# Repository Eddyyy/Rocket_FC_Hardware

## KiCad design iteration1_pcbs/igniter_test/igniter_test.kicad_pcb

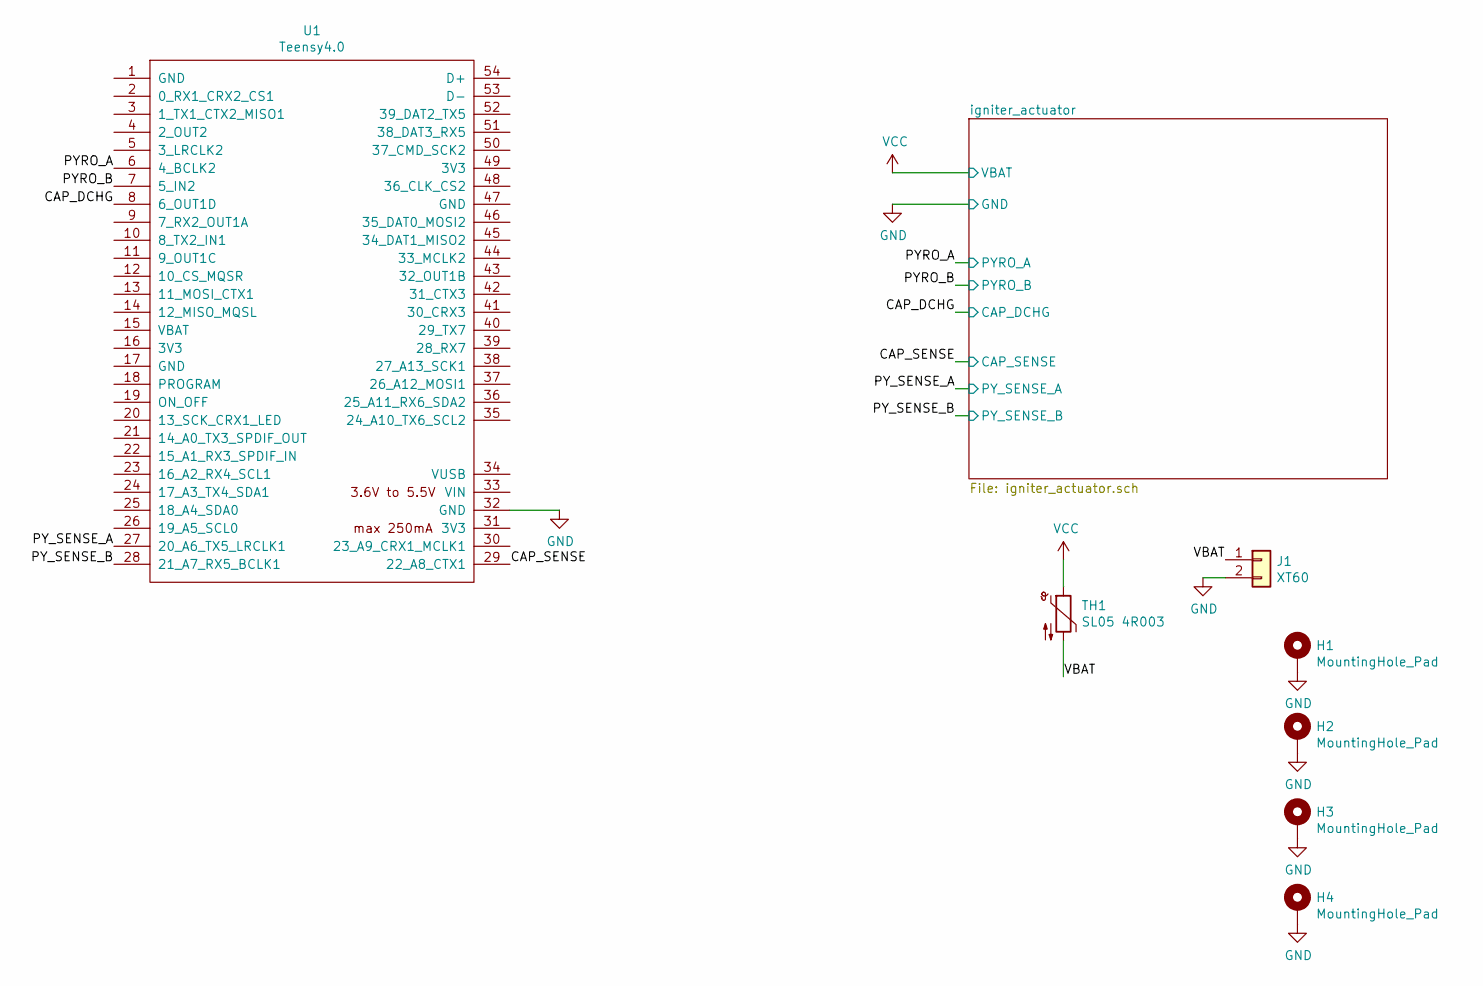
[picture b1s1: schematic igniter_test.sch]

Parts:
H1, H2, H3, H4: MountingHole_Pad; MountingHole_3.2mm_M3_Pad_Via
J1: XT60; AMASS_XT60-M_1x02_P7.20mm_Vertical
TH1: SL05 4R003; SL05_4R003
U1: Teensy4.0; Teensy40

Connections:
/CAP_DCHG: U1.8 (6_OUT1D); also elsewhere on the board
/CAP_SENSE: U1.29 (22_A8_CTX1); also elsewhere on the board
/PYRO_A: U1.6 (4_BCLK2); also elsewhere on the board
/PYRO_B: U1.7 (5_IN2); also elsewhere on the board
/PY_SENSE_A: U1.27 (20_A6_TX5_LRCLK1); also elsewhere on the board
/PY_SENSE_B: U1.28 (21_A7_RX5_BCLK1); also elsewhere on the board
/VBAT: J1.1, TH1.2
GND: H1.1, H2.1, H3.1, H4.1, J1.2, U1.32 (GND); also elsewhere on the board
VCC: TH1.1; also elsewhere on the board

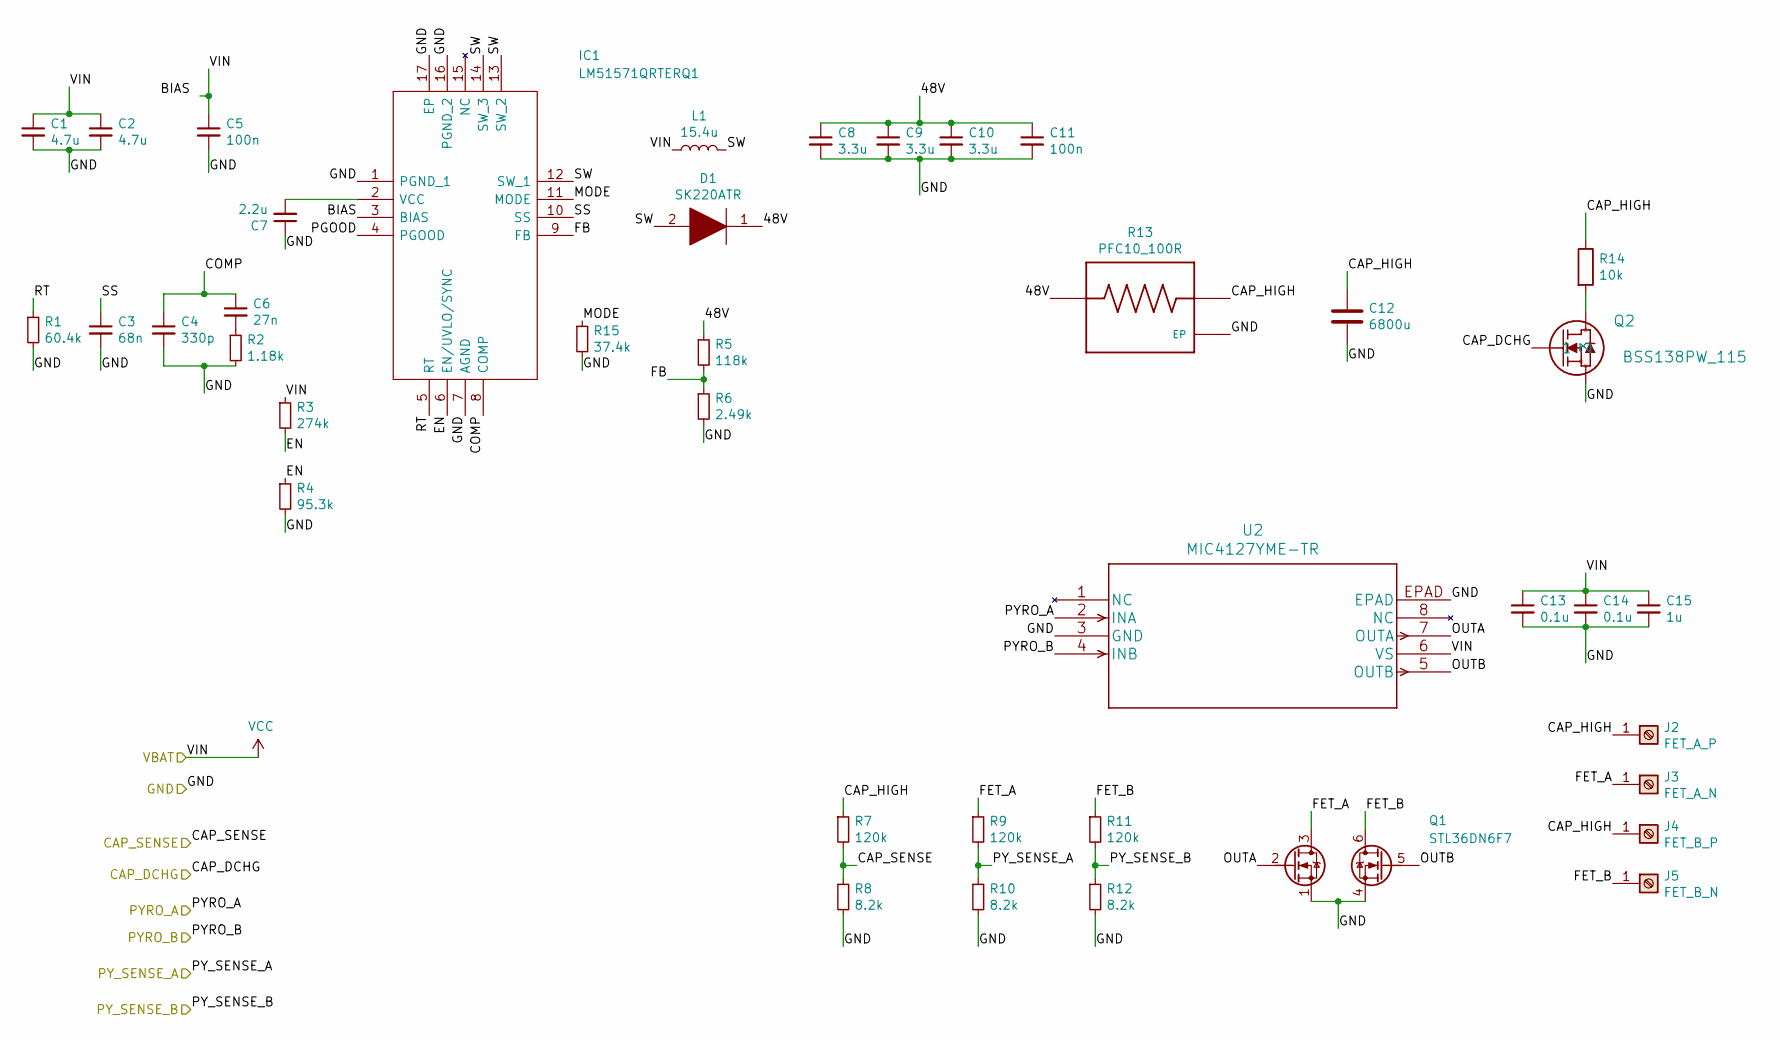
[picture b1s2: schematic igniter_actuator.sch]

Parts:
C1, C2: 4.7u; C_0805_2012Metric_Pad1.18x1.45mm_HandSolder
C3: 68n; C_0603_1608Metric_Pad1.08x0.95mm_HandSolder
C4: 330p; C_0603_1608Metric_Pad1.08x0.95mm_HandSolder
C5, C11: 100n; C_0805_2012Metric_Pad1.18x1.45mm_HandSolder
C6: 27n; C_0805_2012Metric_Pad1.18x1.45mm_HandSolder
C7: 2.2u; C_0805_2012Metric_Pad1.18x1.45mm_HandSolder
C8, C9, C10: 3.3u; C_1206_3216Metric_Pad1.33x1.80mm_HandSolder
C12: 6800u; UVR1H682MRD6
C13, C14: 0.1u; C_0603_1608Metric_Pad1.08x0.95mm_HandSolder
C15: 1u; C_0603_1608Metric_Pad1.08x0.95mm_HandSolder
D1: SK220ATR
IC1: LM51571QRTERQ1
J2: FET_A_P; SM99S01VBNN05G7
J3: FET_A_N; SM99S01VBNN05G7
J4: FET_B_P; SM99S01VBNN05G7
J5: FET_B_N; SM99S01VBNN05G7
L1: 15.4u; L_Wuerth_HCI-1365
Q1: STL36DN6F7; VDFN_5x6
Q2: BSS138PW_115
R1: 60.4k; R_0603_1608Metric_Pad0.98x0.95mm_HandSolder
R2: 1.18k; R_0603_1608Metric_Pad0.98x0.95mm_HandSolder
R3: 274k; R_0603_1608Metric_Pad0.98x0.95mm_HandSolder
R4: 95.3k; R_0603_1608Metric_Pad0.98x0.95mm_HandSolder
R5: 118k; R_0603_1608Metric_Pad0.98x0.95mm_HandSolder
R6: 2.49k; R_0603_1608Metric_Pad0.98x0.95mm_HandSolder
R7, R9, R11: 120k; R_0603_1608Metric_Pad0.98x0.95mm_HandSolder
R8, R10, R12: 8.2k; R_0603_1608Metric_Pad0.98x0.95mm_HandSolder
R13: PFC10_100R; RES_PFC10
R14: 10k; R_0805_2012Metric_Pad1.20x1.40mm_HandSolder
R15: 37.4k; R_0603_1608Metric_Pad0.98x0.95mm_HandSolder
U2: MIC4127YME-TR

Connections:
/CAP_DCHG: Q2.1; also elsewhere on the board
/CAP_SENSE: R7.2, R8.1; also elsewhere on the board
/PYRO_A: U2.2 (INA); also elsewhere on the board
/PYRO_B: U2.4 (INB); also elsewhere on the board
/PY_SENSE_A: R9.2, R10.1; also elsewhere on the board
/PY_SENSE_B: R11.2, R12.1; also elsewhere on the board
/igniter_actuator/48V: C8.1, C9.1, C10.1, C11.1, D1.1, R5.1, R13.1
/igniter_actuator/BIAS: IC1.3 (BIAS)
/igniter_actuator/CAP_HIGH: C12.1, J2.1, J4.1, R7.1, R13.2, R14.1
/igniter_actuator/COMP: C4.1, C6.1, IC1.8 (COMP)
/igniter_actuator/EN: IC1.6 (EN/UVLO/SYNC), R3.2, R4.1
/igniter_actuator/FB: IC1.9 (FB), R5.2, R6.1
/igniter_actuator/FET_A: J3.1, Q1.3 (D), R9.1
/igniter_actuator/FET_B: J5.1, Q1.6 (D), R11.1
/igniter_actuator/MODE: IC1.11 (MODE), R15.1
/igniter_actuator/OUTA: Q1.2 (G), U2.7 (OUTA)
/igniter_actuator/OUTB: Q1.5 (G), U2.5 (OUTB)
/igniter_actuator/PGOOD: IC1.4 (PGOOD)
/igniter_actuator/RT: IC1.5 (RT), R1.1
/igniter_actuator/SS: C3.1, IC1.10 (SS)
/igniter_actuator/SW: D1.2, IC1.12 (SW_1), IC1.13 (SW_2), IC1.14 (SW_3), L1.2
GND: C1.2, C2.2, C3.2, C4.2, C5.2, C7.1, C8.2, C9.2, C10.2, C11.2, C12.2, C13.2, C14.2, C15.2, IC1.1 (PGND_1), IC1.7 (AGND), IC1.16 (PGND_2), IC1.17 (EP), Q1.1 (S), Q1.4 (S), Q2.2, R1.2, R2.2, R4.2, R6.2, R8.2, R10.2, R12.2, R13.3 (EP), R15.2, U2.3 (GND), U2.EPAD; also elsewhere on the board
unnamed: C6.2, R2.1
unnamed: C7.2, IC1.2 (VCC)
unnamed: Q2.3, R14.2
VCC: C1.1, C2.1, C5.1, C13.1, C14.1, C15.1, L1.1, R3.1, U2.6 (VS); also elsewhere on the board

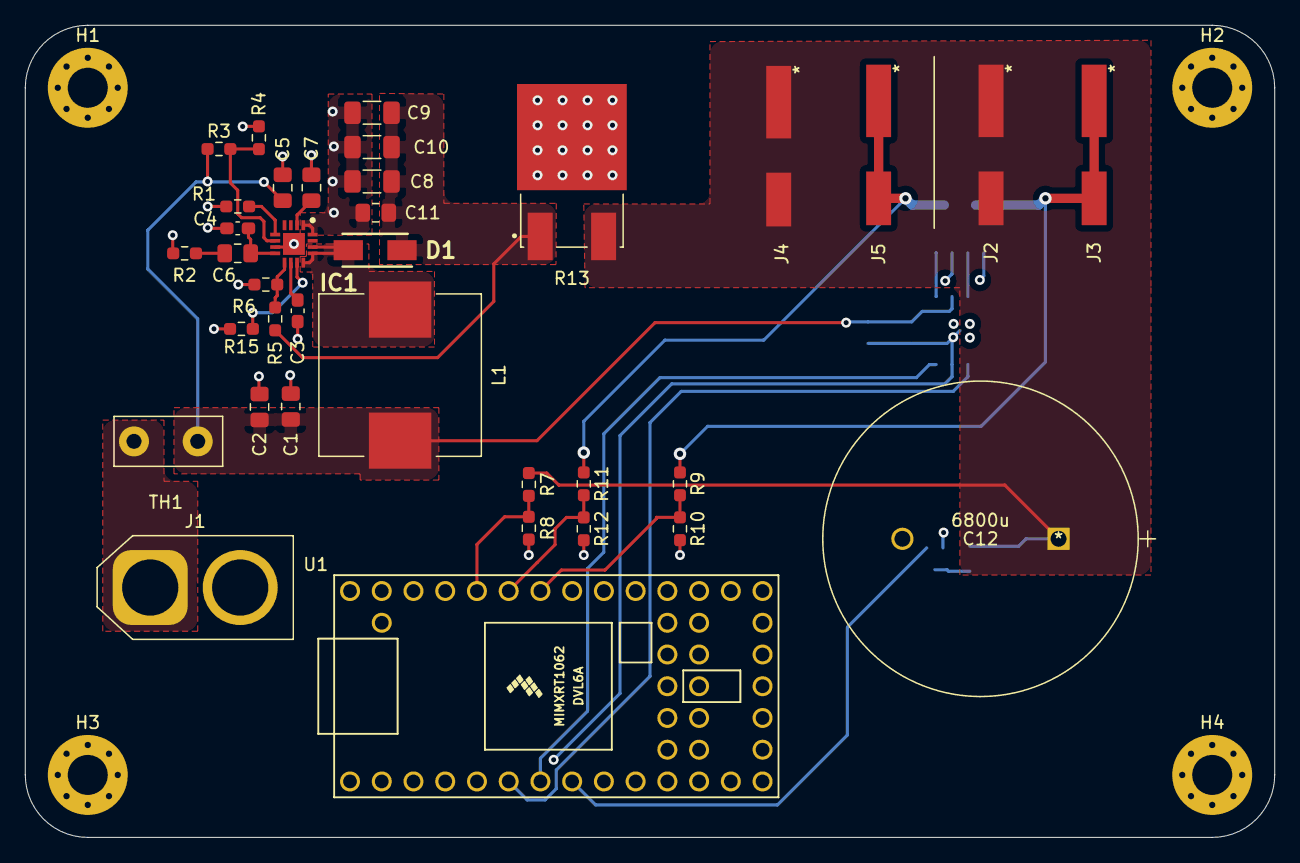
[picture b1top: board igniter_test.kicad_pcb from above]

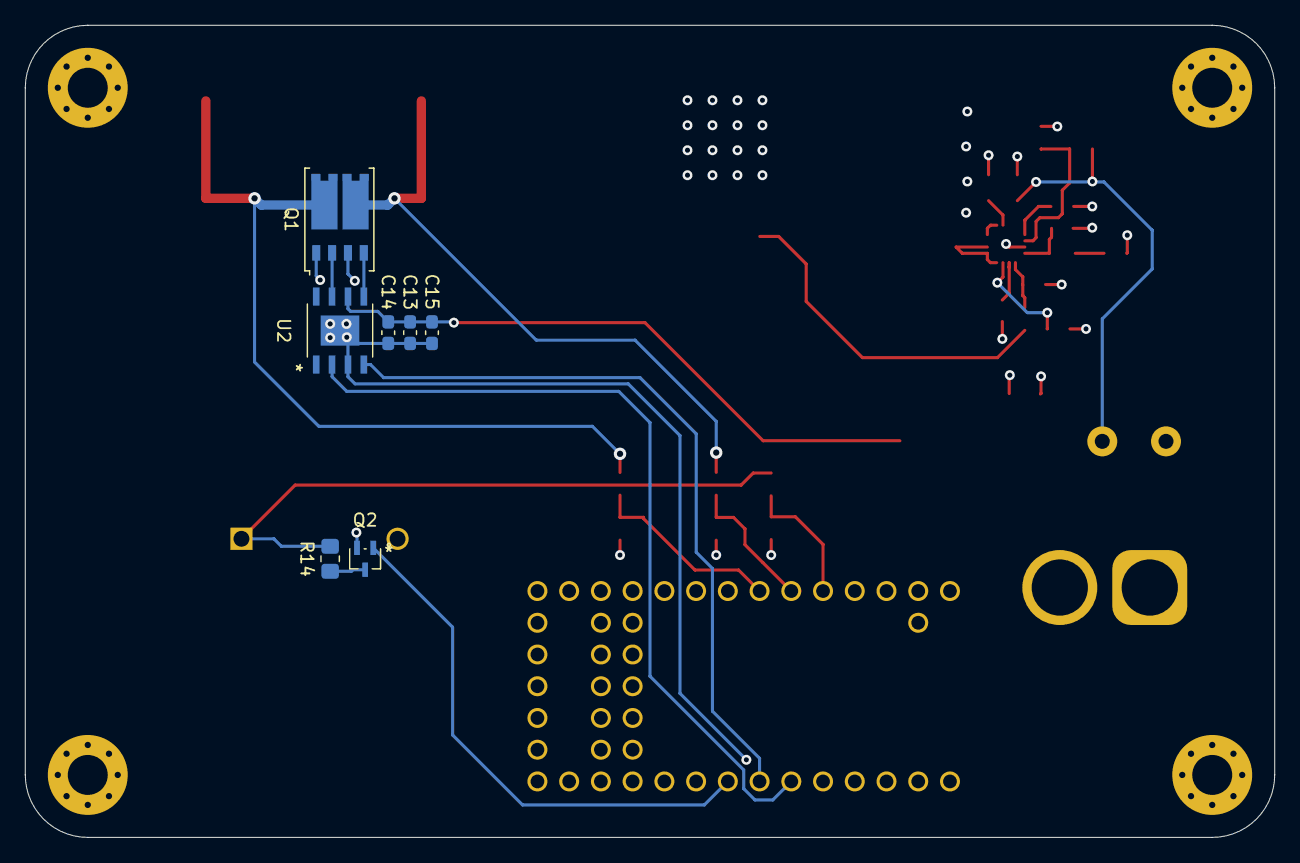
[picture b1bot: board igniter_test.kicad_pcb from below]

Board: 4 copper layers, 100.0 x 65.0 mm, 47 parts (7 on the bottom side), 25 nets.

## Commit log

2021-06-23 Adding files from old repo
2021-06-24 Cleaning individual part files and adding igniter actuator circuits
2021-07-08 Adding schematic work
2021-07-08 Added more library work
2021-07-10 Reorganising pcb folders and adding test pcb
2021-07-11 Starting the igniter pcb
2021-07-13 Adding igniter testing
2021-07-17 Laying out and wiring the igniter test pcb
2021-07-25 igniter test tracks
2021-09-19 Adding most of the changes, almost don

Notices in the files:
parts and their libraries:
Copyright 2021 Accelerated Designs. All rights reserved.
